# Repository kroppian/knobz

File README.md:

## Node Serial Demo

Small Project to demo the connection between an AVR uC and a Javascript script running on node

avrdude -c usbasp -p m328p -U hfuse:w:0b11011001:m -U lfuse:w:0b11110111:m

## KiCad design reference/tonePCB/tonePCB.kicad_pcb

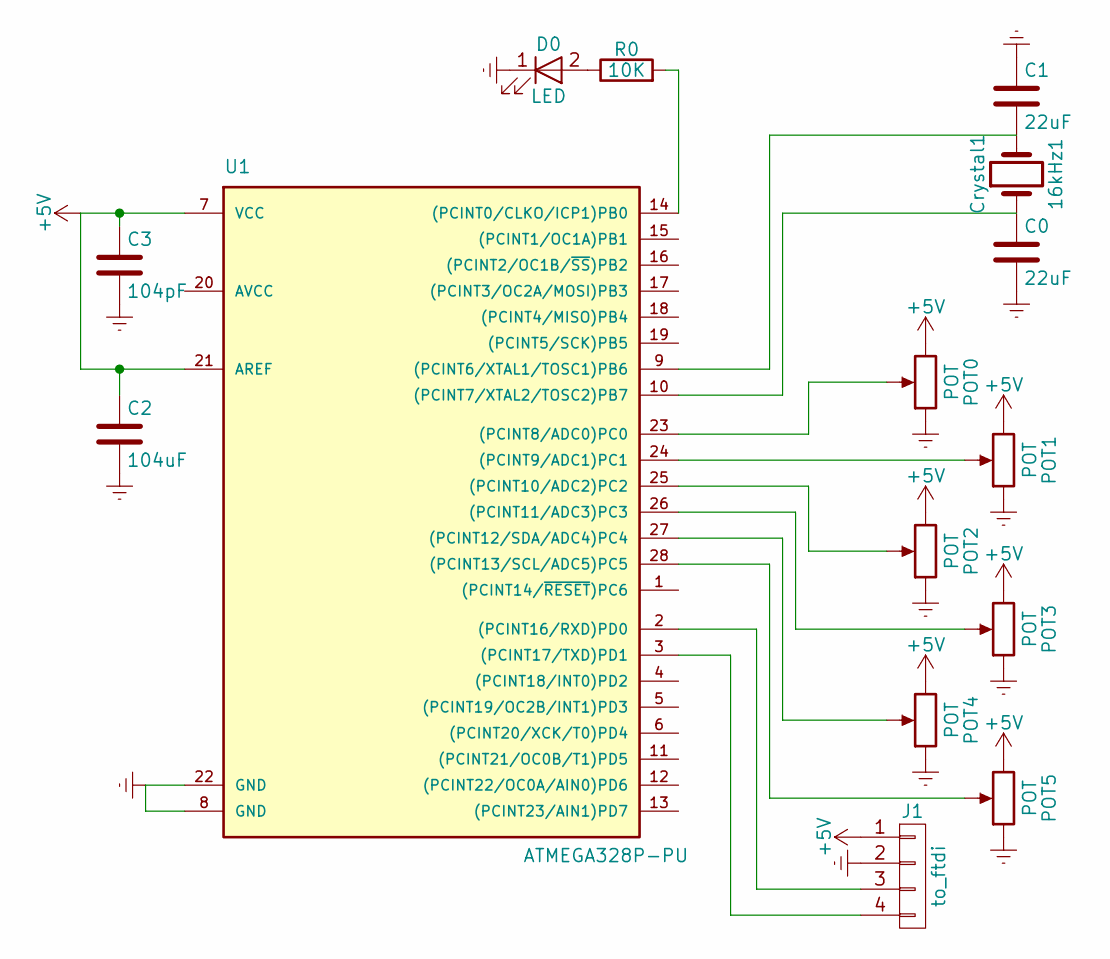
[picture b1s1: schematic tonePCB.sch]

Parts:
C0, C1: 22uF; C_Rect_L4.0mm_W2.5mm_P2.50mm
C2: 104uF; C_Rect_L4.0mm_W2.5mm_P2.50mm
C3: 104pF; C_Rect_L4.0mm_W2.5mm_P2.50mm
Crystal1: 16kHz1; Crystal_HC49-4H_Vertical
D0: LED; LED_D3.0mm_FlatTop
J1: to_ftdi; Socket_Strip_Straight_1x04_Pitch2.54mm
POT0, POT1, POT2, POT3, POT4, POT5: POT; Potentiometer_Trimmer_ACP_CA6h_Vertical
R0: 10K; R_Axial_DIN0204_L3.6mm_D1.6mm_P5.08mm_Horizontal
U1: ATMEGA328P-PU; DIP-28_W7.62mm_Socket

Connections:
+5V: C2.1, C3.1, J1.1, POT0.3, POT1.3, POT2.3, POT3.3, POT4.3, POT5.3, U1.7 (VCC), U1.21 (AREF)
Earth: C0.2, C1.1, C2.2, C3.2, D0.1 (K), J1.2, POT0.1, POT1.1, POT2.1, POT3.1, POT4.1, POT5.1, U1.8 (GND), U1.22 (GND)
unnamed: C0.1, Crystal1.1, U1.10 ((PCINT7/XTAL2/TOSC2)PB7)
unnamed: C1.2, Crystal1.2, U1.9 ((PCINT6/XTAL1/TOSC1)PB6)
unnamed: D0.2 (A), R0.1
unnamed: J1.3, U1.2 ((PCINT16/RXD)PD0)
unnamed: J1.4, U1.3 ((PCINT17/TXD)PD1)
unnamed: POT0.2, U1.23 ((PCINT8/ADC0)PC0)
unnamed: POT1.2, U1.24 ((PCINT9/ADC1)PC1)
unnamed: POT2.2, U1.25 ((PCINT10/ADC2)PC2)
unnamed: POT3.2, U1.26 ((PCINT11/ADC3)PC3)
unnamed: POT4.2, U1.27 ((PCINT12/SDA/ADC4)PC4)
unnamed: POT5.2, U1.28 ((PCINT13/SCL/ADC5)PC5)
unnamed: R0.2, U1.14 ((PCINT0/CLKO/ICP1)PB0)

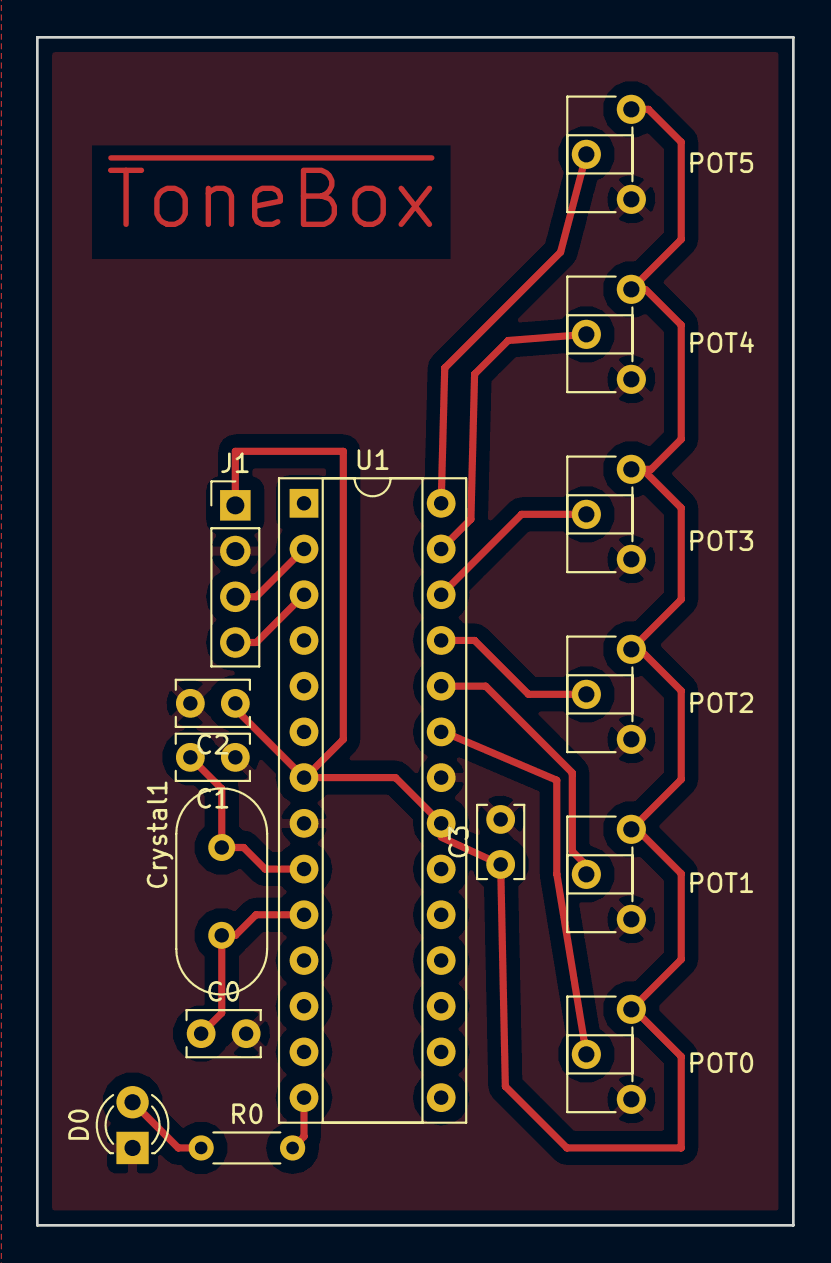
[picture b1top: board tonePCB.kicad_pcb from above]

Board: 2 copper layers, 42.0 x 66.0 mm, 15 parts (0 on the bottom side), 14 nets.

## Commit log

2017-03-04 Initial code commit
2017-03-04 Have two channels going!!!
2017-03-04 Cleaning up the JS code a bit
2017-03-05 Restructuring npm package
2017-03-05 Removing old main script
2017-03-11 Set up events!!!
2017-03-11 Pulling the global frame out of the process data function
2017-03-12 Tearing the process data function apart further
2017-03-12 Cleaning up parameter handling
2017-04-20 Adding library file and a make file
2017-04-20 Adding the main file
2017-04-20 Putting the main file back to its (theoretically) working state
2017-04-20 Adding C files to the git ignore
2017-04-21 Removing compiled files
2017-04-21 Adding fuse writing instructions to README
2017-04-21 Fixing buffer bug
2017-04-21 Getting rid of some old helper code
2017-04-21 Upping the knob count to six
2017-04-21 Adding better comments
2017-04-22 Adding the PCB CAD project
2017-04-22 Adding power and ground copper pours
2017-04-22 Adding an LED to the project
2017-04-22 Removing PDFS renderings from the project
2017-04-25 Last commit before I try and refactor circuit
2017-04-25 Ignoring -bak files
2017-04-25 Removing old backup file
2017-04-25 Removing the back copper and the ground wiring
2017-04-25 Replaced the ground traces with a copper pour
2017-04-25 Reshaping the board to a rectangle
2017-04-26 Widening the clearance between the tracks and the ground pour
